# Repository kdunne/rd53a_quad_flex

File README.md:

# RD53A_quad chip hybrid PCB design files

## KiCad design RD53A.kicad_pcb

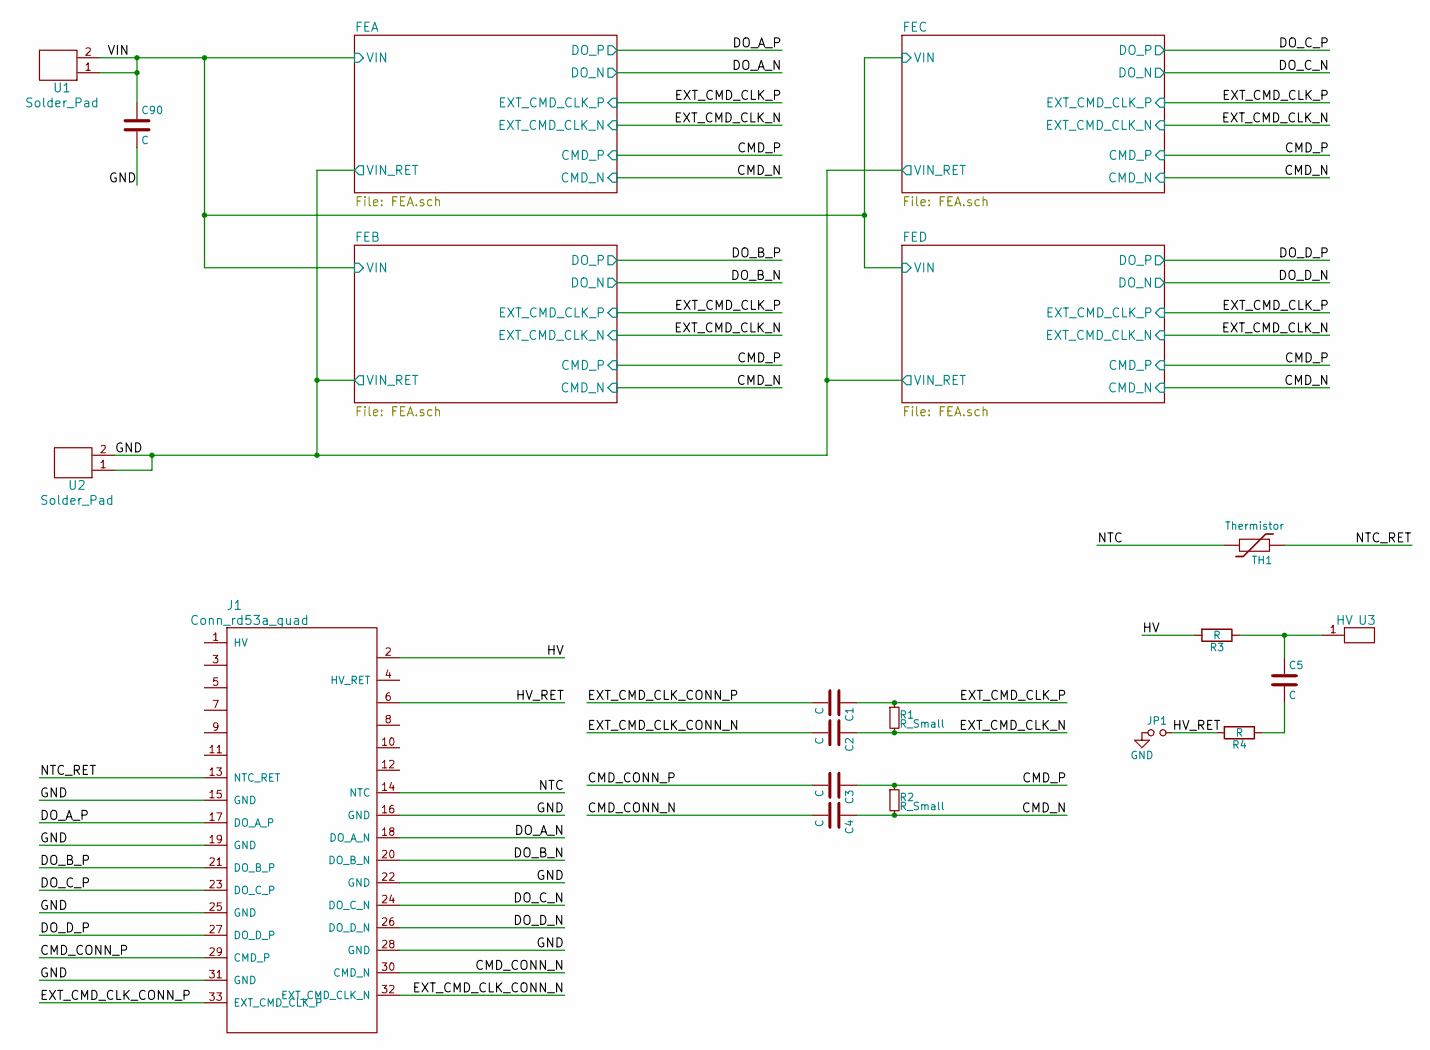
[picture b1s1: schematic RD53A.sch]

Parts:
C1, C2, C3, C4, C90: C; C_0402_NoSilk
C5: C; C_0805
J1: Conn_rd53a_quad; conn
JP1: R_0201_NoSilk
R1, R2: R_Small; R_0402_NoSilk
R3, R4: R; R_0402_NoSilk
TH1: Thermistor; R_0603
U1, U2: Solder_Pad; Power_Pad
U3: HV

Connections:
/CMD_CONN_N: C4.2, J1.30 (CMD_N)
/CMD_CONN_P: C3.2, J1.29 (CMD_P)
/CMD_N: C4.1, R2.2; also elsewhere on the board
/CMD_P: C3.1, R2.1; also elsewhere on the board
/DO_A_N: J1.18 (DO_A_N); also elsewhere on the board
/DO_A_P: J1.17 (DO_A_P); also elsewhere on the board
/DO_B_N: J1.20 (DO_B_N); also elsewhere on the board
/DO_B_P: J1.21 (DO_B_P); also elsewhere on the board
/DO_C_N: J1.24 (DO_C_N); also elsewhere on the board
/DO_C_P: J1.23 (DO_C_P); also elsewhere on the board
/DO_D_N: J1.26 (DO_D_N); also elsewhere on the board
/DO_D_P: J1.27 (DO_D_P); also elsewhere on the board
/EXT_CMD_CLK_CONN_N: C2.2, J1.32 (EXT_CMD_CLK_N)
/EXT_CMD_CLK_CONN_P: C1.2, J1.33 (EXT_CMD_CLK_P)
/EXT_CMD_CLK_N: C2.1, R1.2; also elsewhere on the board
/EXT_CMD_CLK_P: C1.1, R1.1; also elsewhere on the board
/HV: J1.2, R3.2
/HV_RET: J1.6, JP1.2, R4.2
/NTC: J1.14 (NTC), TH1.2
/NTC_RET: J1.13 (NTC_RET), TH1.1
/VIN: C90.1, U1.1, U1.2; also elsewhere on the board
GND: C90.2, J1.15 (GND), J1.16 (GND), J1.19 (GND), J1.22 (GND), J1.25 (GND), J1.28 (GND), J1.31 (GND), JP1.1, U2.1, U2.2; also elsewhere on the board
unnamed: C5.1, R3.1, U3.1
unnamed: C5.2, R4.1

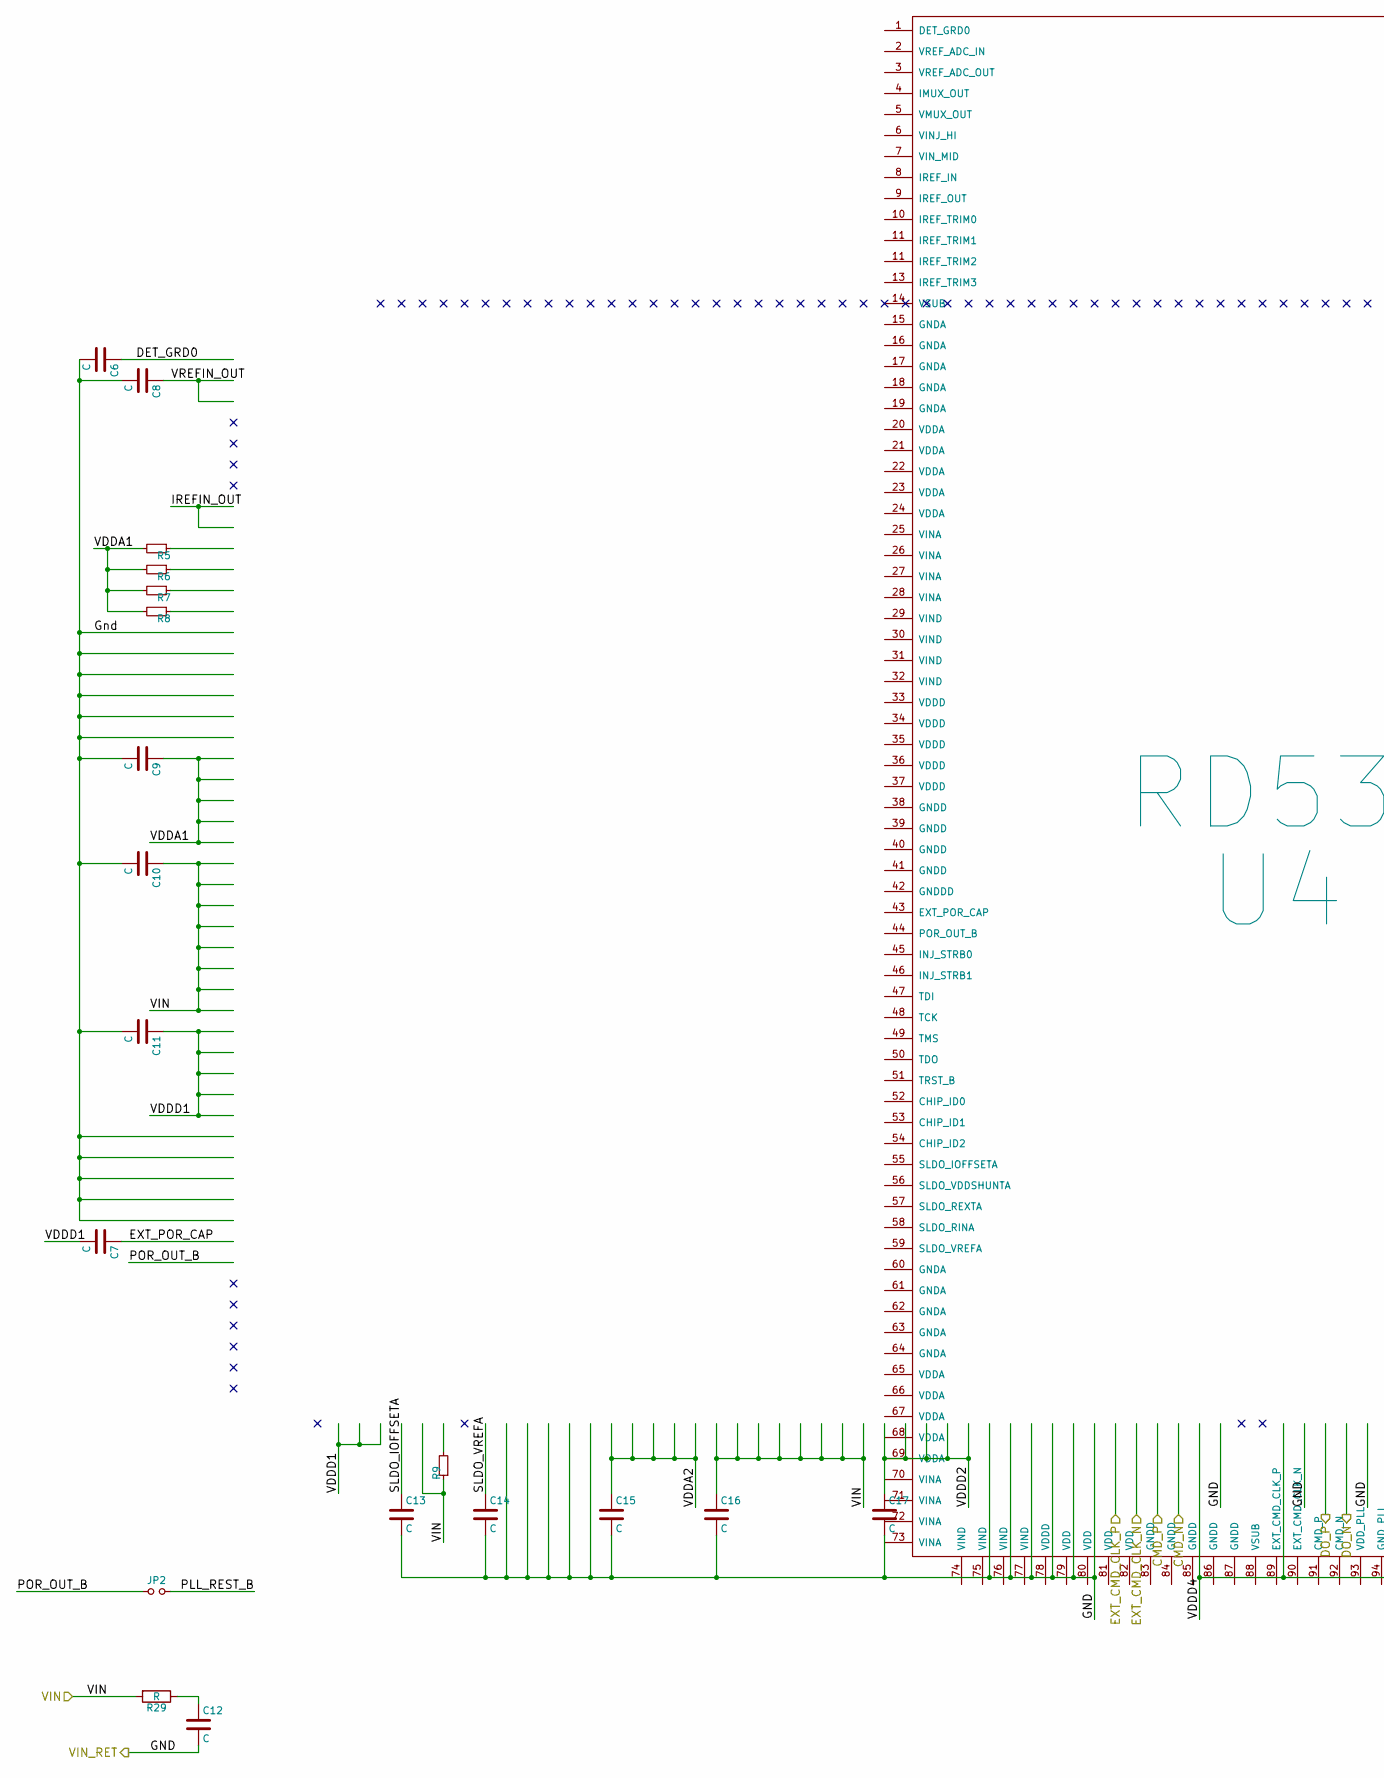
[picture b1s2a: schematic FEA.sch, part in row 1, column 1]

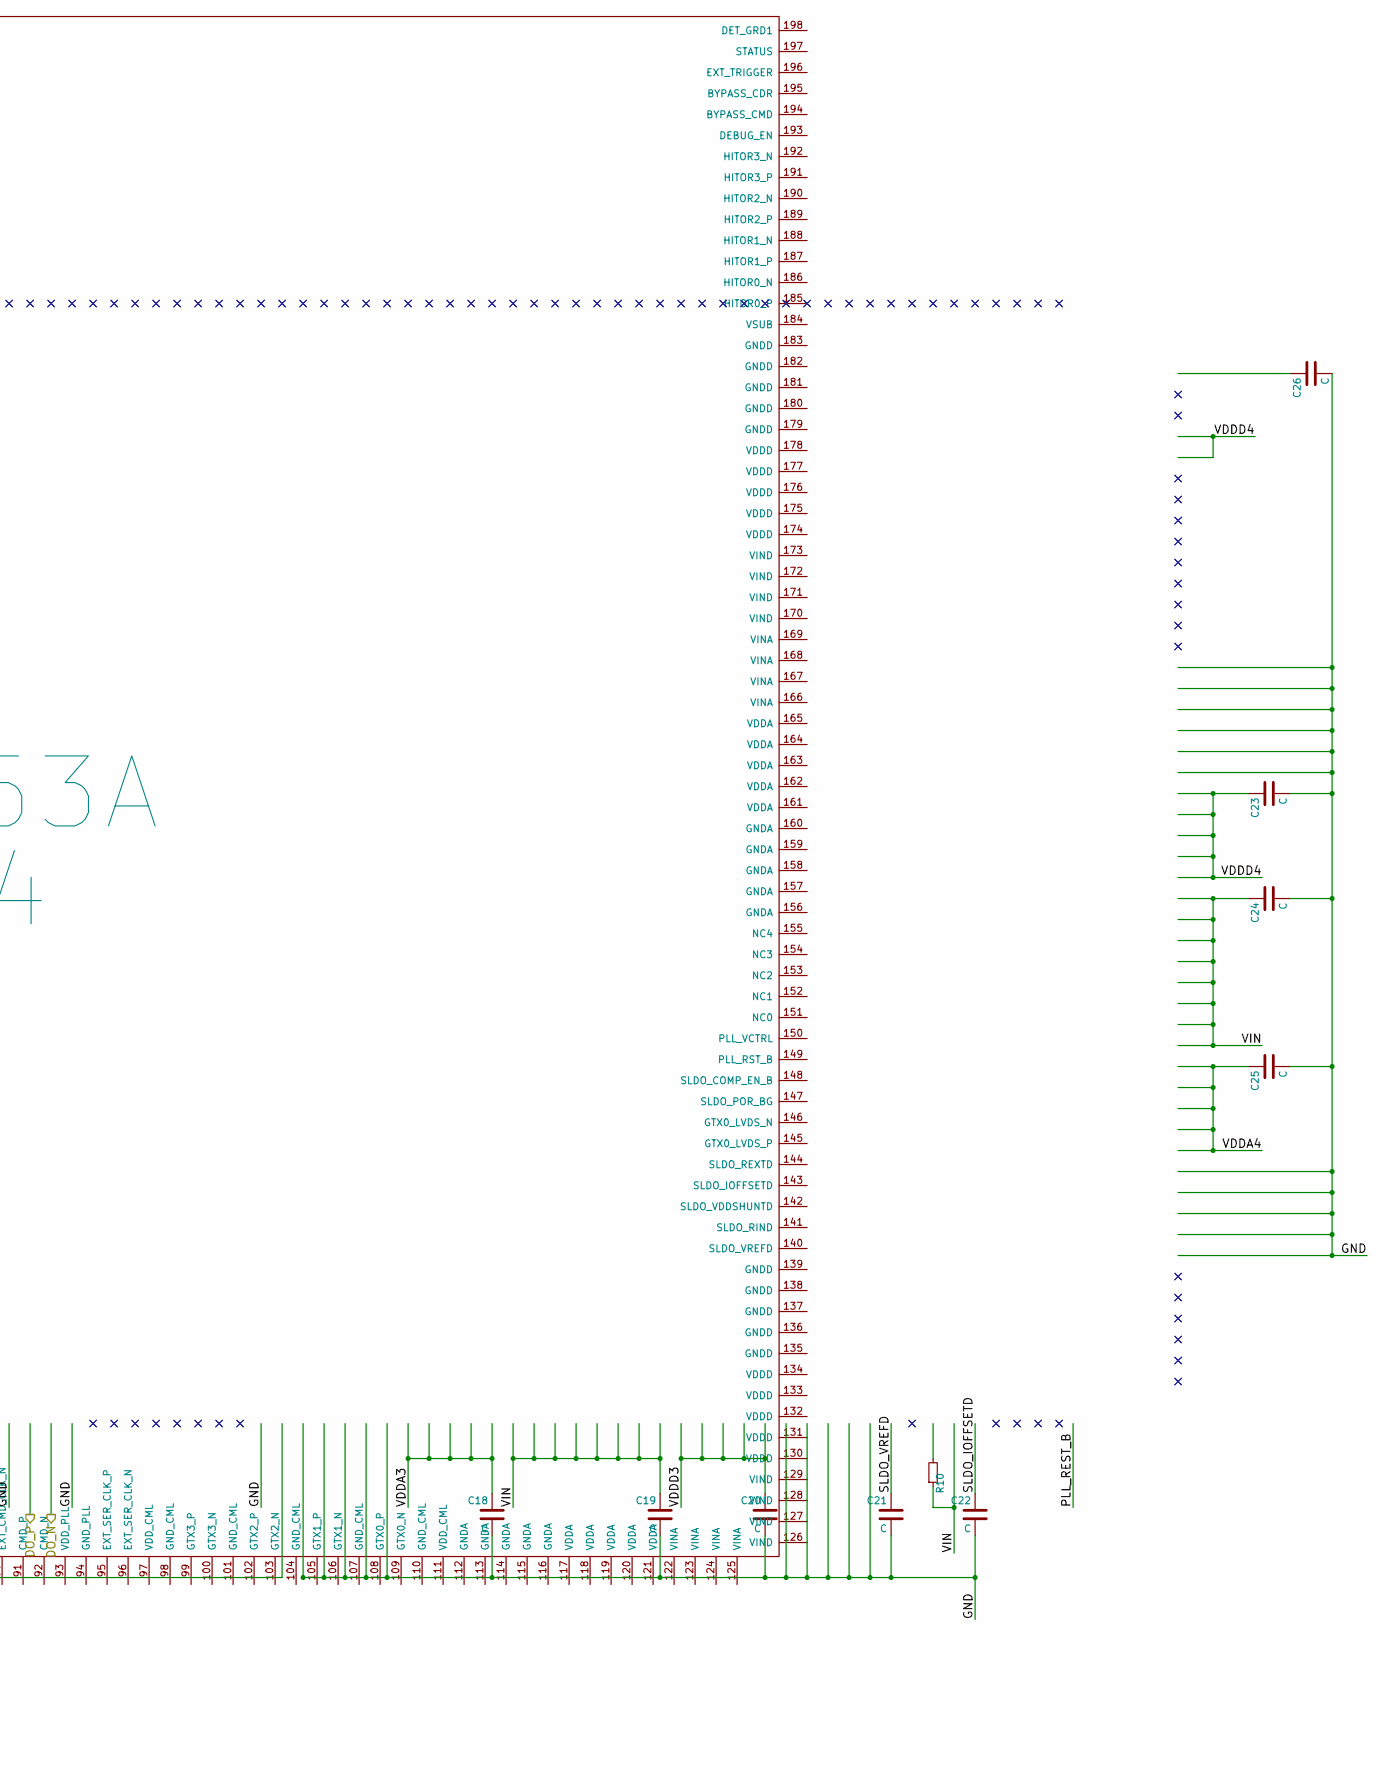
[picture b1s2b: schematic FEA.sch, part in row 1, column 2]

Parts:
C6, C26: C; C_0201_NoSilk
C7, C8, C9, C10, C11, C12, C13, C14, C15, C16, C17, C18, C19, C20, C21, C22, C23, C24, C25: C; C_0402_NoSilk
JP2: C_0201_NoSilk
R5, R6, R7, R8: R_Small; R_0201_NoSilk
R9, R10: R_Small; R_0402_NoSilk
R29: R; R_0402_NoSilk
U4: RD53A; rd53a_wirebonds

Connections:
/CMD_N: U4.92 (CMD_N); also elsewhere on the board
/CMD_P: U4.91 (CMD_P); also elsewhere on the board
/DO_A_N: U4.100 (GTX3_N); also elsewhere on the board
/DO_A_P: U4.99 (GTX3_P); also elsewhere on the board
/EXT_CMD_CLK_N: U4.90 (EXT_CMD_CLK_N); also elsewhere on the board
/EXT_CMD_CLK_P: U4.89 (EXT_CMD_CLK_P); also elsewhere on the board
/FEA/DET_GRD0: C6.1, U4.1 (DET_GRD0)
/FEA/EXT_POR_CAP: C7.1, U4.43 (EXT_POR_CAP)
/FEA/IREFIN_OUT: U4.8 (IREF_IN), U4.9 (IREF_OUT)
/FEA/PLL_REST_B: JP2.2, U4.149 (PLL_RST_B)
/FEA/POR_OUT_B: JP2.1, U4.44 (POR_OUT_B)
/FEA/SLDO_IOFFSETA: C13.1, U4.55 (SLDO_IOFFSETA)
/FEA/SLDO_IOFFSETD: C22.1, U4.144 (SLDO_REXTD)
/FEA/SLDO_VREFA: C14.1, U4.59 (SLDO_VREFA)
/FEA/SLDO_VREFD: C21.1, U4.140 (SLDO_VREFD)
/FEA/VDDA1: C9.1, R5.2, R6.2, R7.2, R8.2, U4.20 (VDDA), U4.21 (VDDA), U4.22 (VDDA), U4.23 (VDDA), U4.24 (VDDA)
/FEA/VDDA3: C18.1, U4.117 (VDDA), U4.118 (VDDA), U4.119 (VDDA), U4.120 (VDDA), U4.121 (VDDA)
/FEA/VDDA4: C25.1, U4.161 (VDDA), U4.162 (VDDA), U4.163 (VDDA), U4.164 (VDDA), U4.165 (VDDA)
/FEA/VDDD1: C7.2, C11.1, U4.33 (VDDD), U4.34 (VDDD), U4.35 (VDDD), U4.36 (VDDD), U4.37 (VDDD), U4.52 (CHIP_ID0), U4.53 (CHIP_ID1), U4.54 (CHIP_ID2)
/FEA/VDDD3: C20.1, U4.130 (VDDD), U4.131 (VDDD), U4.132 (VDDD), U4.133 (VDDD), U4.134 (VDDD)
/FEA/VDDD4: C23.1, U4.93 (VDD_PLL), U4.97 (VDD_CML), U4.111 (VDD_CML), U4.174 (VDDD), U4.175 (VDDD), U4.176 (VDDD), U4.177 (VDDD), U4.178 (VDDD), U4.194 (BYPASS_CMD), U4.195 (BYPASS_CDR)
/FEA/VREFIN_OUT: C8.1, U4.2 (VREF_ADC_IN), U4.3 (VREF_ADC_OUT)
/VIN: C10.1, C16.1, C19.1, C24.1, R9.1, R10.1, R29.2, U4.25 (VINA), U4.26 (VINA), U4.27 (VINA), U4.28 (VINA), U4.29 (VIND), U4.30 (VIND), U4.31 (VIND), U4.32 (VIND), U4.56 (SLDO_VDDSHUNTA), U4.70 (VINA), U4.71 (VINA), U4.72 (VINA), U4.73 (VINA), U4.74 (VIND), U4.75 (VIND), U4.76 (VIND), U4.77 (VIND), U4.122 (VINA), U4.123 (VINA), U4.124 (VINA), U4.125 (VINA), U4.126 (VIND), U4.127 (VIND), U4.128 (VIND), U4.129 (VIND), U4.143 (SLDO_IOFFSETD), U4.166 (VINA), U4.167 (VINA), U4.168 (VINA), U4.169 (VINA), U4.170 (VIND), U4.171 (VIND), U4.172 (VIND), U4.173 (VIND); also elsewhere on the board
GND: C6.2, C8.2, C9.2, C10.2, C11.2, C12.2, C13.2, C14.2, C15.2, C16.2, C17.2, C18.2, C19.2, C20.2, C21.2, C22.2, C23.2, C24.2, C25.2, C26.2, U4.14 (VSUB), U4.15 (GNDA), U4.16 (GNDA), U4.17 (GNDA), U4.18 (GNDA), U4.19 (GNDA), U4.38 (GNDD), U4.39 (GNDD), U4.40 (GNDD), U4.41 (GNDD), U4.42 (GNDDD), U4.60 (GNDA), U4.61 (GNDA), U4.62 (GNDA), U4.63 (GNDA), U4.64 (GNDA), U4.83 (GNDD), U4.84 (GNDD), U4.85 (GNDD), U4.86 (GNDD), U4.87 (GNDD), U4.88 (VSUB), U4.94 (GND_PLL), U4.98 (GND_CML), U4.101 (GND_CML), U4.110 (GND_CML), U4.112 (GNDA), U4.113 (GNDA), U4.114 (GNDA), U4.115 (GNDA), U4.116 (GNDA), U4.135 (GNDD), U4.136 (GNDD), U4.137 (GNDD), U4.138 (GNDD), U4.139 (GNDD), U4.156 (GNDA), U4.157 (GNDA), U4.158 (GNDA), U4.159 (GNDA), U4.160 (GNDA), U4.179 (GNDD), U4.180 (GNDD), U4.181 (GNDD), U4.182 (GNDD), U4.183 (GNDD), U4.184 (VSUB); also elsewhere on the board
unnamed: C12.1, R29.1
unnamed: C26.1, U4.198 (DET_GRD1)
unnamed: R5.1, U4.10 (IREF_TRIM0)
unnamed: R6.1, U4.11 (IREF_TRIM1)
unnamed: R7.1, U4.12 (IREF_TRIM2)
unnamed: R8.1, U4.13 (IREF_TRIM3)
unnamed: R9.2, U4.57 (SLDO_REXTA)
unnamed: R10.2, U4.142 (SLDO_VDDSHUNTD)

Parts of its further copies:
C27, C47, C48, C68, C69, C89: C; C_0201_NoSilk
C28, C29, C30, C31, C32, C33, C34, C35, C36, C37, C38, C39, C40, C41, C42, C43, C44, C45, C46, C49, C50, C51, C52, C53, C54, C55, C56, C57, C58, C59, C60, C61, C62, C63, C64, C65, C66, C67, C70, C71, C72, C73, C74, C75, C76, C77, C78, C79, C80, C81, C82, C83, C84, C85, C86, C87, C88: C; C_0402_NoSilk
JP3, JP4, JP5: C_0201_NoSilk
R11, R12, R13, R14, R17, R18, R19, R20, R23, R24, R25, R26: R_Small; R_0201_NoSilk
R15, R16, R21, R22, R27, R28: R_Small; R_0402_NoSilk
R30, R31, R32: R; R_0402_NoSilk
U5, U6, U7: RD53A; rd53a_wirebonds

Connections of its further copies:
/CMD_N: U5.92 (CMD_N), U6.92 (CMD_N), U7.92 (CMD_N); also elsewhere on the board
/CMD_P: U5.91 (CMD_P), U6.91 (CMD_P), U7.91 (CMD_P); also elsewhere on the board
/DO_B_N: U5.100 (GTX3_N); also elsewhere on the board
/DO_B_P: U5.99 (GTX3_P); also elsewhere on the board
/DO_C_N: U6.100 (GTX3_N); also elsewhere on the board
/DO_C_P: U6.99 (GTX3_P); also elsewhere on the board
/DO_D_N: U7.100 (GTX3_N); also elsewhere on the board
/DO_D_P: U7.99 (GTX3_P); also elsewhere on the board
/EXT_CMD_CLK_N: U5.90 (EXT_CMD_CLK_N), U6.90 (EXT_CMD_CLK_N), U7.90 (EXT_CMD_CLK_N); also elsewhere on the board
/EXT_CMD_CLK_P: U5.89 (EXT_CMD_CLK_P), U6.89 (EXT_CMD_CLK_P), U7.89 (EXT_CMD_CLK_P); also elsewhere on the board
/FEB/DET_GRD0: C27.1, U5.1 (DET_GRD0)
/FEB/EXT_POR_CAP: C28.1, U5.43 (EXT_POR_CAP)
/FEB/IREFIN_OUT: U5.8 (IREF_IN), U5.9 (IREF_OUT)
/FEB/PLL_REST_B: JP3.2, U5.149 (PLL_RST_B)
/FEB/POR_OUT_B: JP3.1, U5.44 (POR_OUT_B)
/FEB/SLDO_IOFFSETA: C34.1, U5.55 (SLDO_IOFFSETA)
/FEB/SLDO_IOFFSETD: C43.1, U5.144 (SLDO_REXTD)
/FEB/SLDO_VREFA: C35.1, U5.59 (SLDO_VREFA)
/FEB/SLDO_VREFD: C42.1, U5.140 (SLDO_VREFD)
/FEB/VDDA1: C30.1, R11.2, R12.2, R13.2, R14.2, U5.20 (VDDA), U5.21 (VDDA), U5.22 (VDDA), U5.23 (VDDA), U5.24 (VDDA)
/FEB/VDDA2: C36.1, U5.65 (VDDA), U5.66 (VDDA), U5.67 (VDDA), U5.68 (VDDA), U5.69 (VDDA)
/FEB/VDDA3: C39.1, U5.117 (VDDA), U5.118 (VDDA), U5.119 (VDDA), U5.120 (VDDA), U5.121 (VDDA)
/FEB/VDDA4: C46.1, U5.161 (VDDA), U5.162 (VDDA), U5.163 (VDDA), U5.164 (VDDA), U5.165 (VDDA)
/FEB/VDDD1: C28.2, C32.1, U5.33 (VDDD), U5.34 (VDDD), U5.35 (VDDD), U5.36 (VDDD), U5.37 (VDDD), U5.52 (CHIP_ID0), U5.53 (CHIP_ID1), U5.54 (CHIP_ID2)
/FEB/VDDD2: C38.1, U5.78 (VDDD), U5.79 (VDD), U5.80 (VDD), U5.81 (VDD), U5.82 (VDD)
/FEB/VDDD3: C41.1, U5.130 (VDDD), U5.131 (VDDD), U5.132 (VDDD), U5.133 (VDDD), U5.134 (VDDD)
/FEB/VDDD4: C44.1, U5.93 (VDD_PLL), U5.97 (VDD_CML), U5.111 (VDD_CML), U5.174 (VDDD), U5.175 (VDDD), U5.176 (VDDD), U5.177 (VDDD), U5.178 (VDDD), U5.194 (BYPASS_CMD), U5.195 (BYPASS_CDR)
/FEB/VREFIN_OUT: C29.1, U5.2 (VREF_ADC_IN), U5.3 (VREF_ADC_OUT)
/FEC/DET_GRD0: C48.1, U6.1 (DET_GRD0)
/FEC/EXT_POR_CAP: C49.1, U6.43 (EXT_POR_CAP)
/FEC/IREFIN_OUT: U6.8 (IREF_IN), U6.9 (IREF_OUT)
/FEC/PLL_REST_B: JP4.2, U6.149 (PLL_RST_B)
/FEC/POR_OUT_B: JP4.1, U6.44 (POR_OUT_B)
/FEC/SLDO_IOFFSETA: C55.1, U6.55 (SLDO_IOFFSETA)
/FEC/SLDO_IOFFSETD: C64.1, U6.144 (SLDO_REXTD)
/FEC/SLDO_VREFA: C56.1, U6.59 (SLDO_VREFA)
/FEC/SLDO_VREFD: C63.1, U6.140 (SLDO_VREFD)
/FEC/VDDA1: C51.1, R17.2, R18.2, R19.2, R20.2, U6.20 (VDDA), U6.21 (VDDA), U6.22 (VDDA), U6.23 (VDDA), U6.24 (VDDA)
/FEC/VDDA2: C57.1, U6.65 (VDDA), U6.66 (VDDA), U6.67 (VDDA), U6.68 (VDDA), U6.69 (VDDA)
/FEC/VDDA3: C60.1, U6.117 (VDDA), U6.118 (VDDA), U6.119 (VDDA), U6.120 (VDDA), U6.121 (VDDA)
/FEC/VDDA4: C67.1, U6.161 (VDDA), U6.162 (VDDA), U6.163 (VDDA), U6.164 (VDDA), U6.165 (VDDA)
/FEC/VDDD1: C49.2, C53.1, U6.33 (VDDD), U6.34 (VDDD), U6.35 (VDDD), U6.36 (VDDD), U6.37 (VDDD), U6.52 (CHIP_ID0), U6.53 (CHIP_ID1), U6.54 (CHIP_ID2)
/FEC/VDDD2: C59.1, U6.78 (VDDD), U6.79 (VDD), U6.80 (VDD), U6.81 (VDD), U6.82 (VDD)
/FEC/VDDD3: C62.1, U6.130 (VDDD), U6.131 (VDDD), U6.132 (VDDD), U6.133 (VDDD), U6.134 (VDDD)
/FEC/VDDD4: C65.1, U6.93 (VDD_PLL), U6.97 (VDD_CML), U6.111 (VDD_CML), U6.174 (VDDD), U6.175 (VDDD), U6.176 (VDDD), U6.177 (VDDD), U6.178 (VDDD), U6.194 (BYPASS_CMD), U6.195 (BYPASS_CDR)
/FEC/VREFIN_OUT: C50.1, U6.2 (VREF_ADC_IN), U6.3 (VREF_ADC_OUT)
/FED/DET_GRD0: C69.1, U7.1 (DET_GRD0)
/FED/EXT_POR_CAP: C70.1, U7.43 (EXT_POR_CAP)
/FED/IREFIN_OUT: U7.8 (IREF_IN), U7.9 (IREF_OUT)
/FED/PLL_REST_B: JP5.2, U7.149 (PLL_RST_B)
/FED/POR_OUT_B: JP5.1, U7.44 (POR_OUT_B)
/FED/SLDO_IOFFSETA: C76.1, U7.55 (SLDO_IOFFSETA)
/FED/SLDO_IOFFSETD: C85.1, U7.144 (SLDO_REXTD)
/FED/SLDO_VREFA: C77.1, U7.59 (SLDO_VREFA)
/FED/SLDO_VREFD: C84.1, U7.140 (SLDO_VREFD)
/FED/VDDA1: C72.1, R23.2, R24.2, R25.2, R26.2, U7.20 (VDDA), U7.21 (VDDA), U7.22 (VDDA), U7.23 (VDDA), U7.24 (VDDA)
/FED/VDDA2: C78.1, U7.65 (VDDA), U7.66 (VDDA), U7.67 (VDDA), U7.68 (VDDA), U7.69 (VDDA)
/FED/VDDA3: C81.1, U7.117 (VDDA), U7.118 (VDDA), U7.119 (VDDA), U7.120 (VDDA), U7.121 (VDDA)
/FED/VDDA4: C88.1, U7.161 (VDDA), U7.162 (VDDA), U7.163 (VDDA), U7.164 (VDDA), U7.165 (VDDA)
/FED/VDDD1: C70.2, C74.1, U7.33 (VDDD), U7.34 (VDDD), U7.35 (VDDD), U7.36 (VDDD), U7.37 (VDDD), U7.52 (CHIP_ID0), U7.53 (CHIP_ID1), U7.54 (CHIP_ID2)
/FED/VDDD2: C80.1, U7.78 (VDDD), U7.79 (VDD), U7.80 (VDD), U7.81 (VDD), U7.82 (VDD)
/FED/VDDD3: C83.1, U7.130 (VDDD), U7.131 (VDDD), U7.132 (VDDD), U7.133 (VDDD), U7.134 (VDDD)
/FED/VDDD4: C86.1, U7.93 (VDD_PLL), U7.97 (VDD_CML), U7.111 (VDD_CML), U7.174 (VDDD), U7.175 (VDDD), U7.176 (VDDD), U7.177 (VDDD), U7.178 (VDDD), U7.194 (BYPASS_CMD), U7.195 (BYPASS_CDR)
/FED/VREFIN_OUT: C71.1, U7.2 (VREF_ADC_IN), U7.3 (VREF_ADC_OUT)
/VIN: C31.1, C37.1, C40.1, C45.1, C52.1, C58.1, C61.1, C66.1, C73.1, C79.1, C82.1, C87.1, R15.1, R16.1, R21.1, R22.1, R27.1, R28.1, R30.2, R31.2, R32.2, U5.25 (VINA), U5.26 (VINA), U5.27 (VINA), U5.28 (VINA), U5.29 (VIND), U5.30 (VIND), U5.31 (VIND), U5.32 (VIND), U5.56 (SLDO_VDDSHUNTA), U5.70 (VINA), U5.71 (VINA), U5.72 (VINA), U5.73 (VINA), U5.74 (VIND), U5.75 (VIND), U5.76 (VIND), U5.77 (VIND), U5.122 (VINA), U5.123 (VINA), U5.124 (VINA), U5.125 (VINA), U5.126 (VIND), U5.127 (VIND), U5.128 (VIND), U5.129 (VIND), U5.143 (SLDO_IOFFSETD), U5.166 (VINA), U5.167 (VINA), U5.168 (VINA), U5.169 (VINA), U5.170 (VIND), U5.171 (VIND), U5.172 (VIND), U5.173 (VIND), U6.25 (VINA), U6.26 (VINA), U6.27 (VINA), U6.28 (VINA), U6.29 (VIND), U6.30 (VIND), U6.31 (VIND), U6.32 (VIND), U6.56 (SLDO_VDDSHUNTA), U6.70 (VINA), U6.71 (VINA), U6.72 (VINA), U6.73 (VINA), U6.74 (VIND), U6.75 (VIND), U6.76 (VIND), U6.77 (VIND), U6.122 (VINA), U6.123 (VINA), U6.124 (VINA), U6.125 (VINA), U6.126 (VIND), U6.127 (VIND), U6.128 (VIND), U6.129 (VIND), U6.143 (SLDO_IOFFSETD), U6.166 (VINA), U6.167 (VINA), U6.168 (VINA), U6.169 (VINA), U6.170 (VIND), U6.171 (VIND), U6.172 (VIND), U6.173 (VIND), U7.25 (VINA), U7.26 (VINA), U7.27 (VINA), U7.28 (VINA), U7.29 (VIND), U7.30 (VIND), U7.31 (VIND), U7.32 (VIND), U7.56 (SLDO_VDDSHUNTA), U7.70 (VINA), U7.71 (VINA), U7.72 (VINA), U7.73 (VINA), U7.74 (VIND), U7.75 (VIND), U7.76 (VIND), U7.77 (VIND), U7.122 (VINA), U7.123 (VINA), U7.124 (VINA), U7.125 (VINA), U7.126 (VIND), U7.127 (VIND), U7.128 (VIND), U7.129 (VIND), U7.143 (SLDO_IOFFSETD), U7.166 (VINA), U7.167 (VINA), U7.168 (VINA), U7.169 (VINA), U7.170 (VIND), U7.171 (VIND), U7.172 (VIND), U7.173 (VIND); also elsewhere on the board
GND: C27.2, C29.2, C30.2, C31.2, C32.2, C33.2, C34.2, C35.2, C36.2, C37.2, C38.2, C39.2, C40.2, C41.2, C42.2, C43.2, C44.2, C45.2, C46.2, C47.2, C48.2, C50.2, C51.2, C52.2, C53.2, C54.2, C55.2, C56.2, C57.2, C58.2, C59.2, C60.2, C61.2, C62.2, C63.2, C64.2, C65.2, C66.2, C67.2, C68.2, C69.2, C71.2, C72.2, C73.2, C74.2, C75.2, C76.2, C77.2, C78.2, C79.2, C80.2, C81.2, C82.2, C83.2, C84.2, C85.2, C86.2, C87.2, C88.2, C89.2, U5.14 (VSUB), U5.15 (GNDA), U5.16 (GNDA), U5.17 (GNDA), U5.18 (GNDA), U5.19 (GNDA), U5.38 (GNDD), U5.39 (GNDD), U5.40 (GNDD), U5.41 (GNDD), U5.42 (GNDDD), U5.60 (GNDA), U5.61 (GNDA), U5.62 (GNDA), U5.63 (GNDA), U5.64 (GNDA), U5.83 (GNDD), U5.84 (GNDD), U5.85 (GNDD), U5.86 (GNDD), U5.87 (GNDD), U5.88 (VSUB), U5.94 (GND_PLL), U5.98 (GND_CML), U5.101 (GND_CML), U5.110 (GND_CML), U5.112 (GNDA), U5.113 (GNDA), U5.114 (GNDA), U5.115 (GNDA), U5.116 (GNDA), U5.135 (GNDD), U5.136 (GNDD), U5.137 (GNDD), U5.138 (GNDD), U5.139 (GNDD), U5.156 (GNDA), U5.157 (GNDA), U5.158 (GNDA), U5.159 (GNDA), U5.160 (GNDA), U5.179 (GNDD), U5.180 (GNDD), U5.181 (GNDD), U5.182 (GNDD), U5.183 (GNDD), U5.184 (VSUB), U6.14 (VSUB), U6.15 (GNDA), U6.16 (GNDA), U6.17 (GNDA), U6.18 (GNDA), U6.19 (GNDA), U6.38 (GNDD), U6.39 (GNDD), U6.40 (GNDD), U6.41 (GNDD), U6.42 (GNDDD), U6.60 (GNDA), U6.61 (GNDA), U6.62 (GNDA), U6.63 (GNDA), U6.64 (GNDA), U6.83 (GNDD), U6.84 (GNDD), U6.85 (GNDD), U6.86 (GNDD), U6.87 (GNDD), U6.88 (VSUB), U6.94 (GND_PLL), U6.98 (GND_CML), U6.101 (GND_CML), U6.110 (GND_CML), U6.112 (GNDA), U6.113 (GNDA), U6.114 (GNDA), U6.115 (GNDA), U6.116 (GNDA), U6.135 (GNDD), U6.136 (GNDD), U6.137 (GNDD), U6.138 (GNDD), U6.139 (GNDD), U6.156 (GNDA), U6.157 (GNDA), U6.158 (GNDA), U6.159 (GNDA), U6.160 (GNDA), U6.179 (GNDD), U6.180 (GNDD), U6.181 (GNDD), U6.182 (GNDD), U6.183 (GNDD), U6.184 (VSUB), U7.14 (VSUB), U7.15 (GNDA), U7.16 (GNDA), U7.17 (GNDA), U7.18 (GNDA), U7.19 (GNDA), U7.38 (GNDD), U7.39 (GNDD), U7.40 (GNDD), U7.41 (GNDD), U7.42 (GNDDD), U7.60 (GNDA), U7.61 (GNDA), U7.62 (GNDA), U7.63 (GNDA), U7.64 (GNDA), U7.83 (GNDD), U7.84 (GNDD), U7.85 (GNDD), U7.86 (GNDD), U7.87 (GNDD), U7.88 (VSUB), U7.94 (GND_PLL), U7.98 (GND_CML), U7.101 (GND_CML), U7.110 (GND_CML), U7.112 (GNDA), U7.113 (GNDA), U7.114 (GNDA), U7.115 (GNDA), U7.116 (GNDA), U7.135 (GNDD), U7.136 (GNDD), U7.137 (GNDD), U7.138 (GNDD), U7.139 (GNDD), U7.156 (GNDA), U7.157 (GNDA), U7.158 (GNDA), U7.159 (GNDA), U7.160 (GNDA), U7.179 (GNDD), U7.180 (GNDD), U7.181 (GNDD), U7.182 (GNDD), U7.183 (GNDD), U7.184 (VSUB); also elsewhere on the board
unnamed: C33.1, R30.1
unnamed: C47.1, U5.198 (DET_GRD1)
unnamed: C54.1, R31.1
unnamed: C68.1, U6.198 (DET_GRD1)
unnamed: C75.1, R32.1
unnamed: C89.1, U7.198 (DET_GRD1)
unnamed: R11.1, U5.10 (IREF_TRIM0)
unnamed: R12.1, U5.11 (IREF_TRIM1)
unnamed: R13.1, U5.12 (IREF_TRIM2)
unnamed: R14.1, U5.13 (IREF_TRIM3)
unnamed: R15.2, U5.57 (SLDO_REXTA)
unnamed: R16.2, U5.142 (SLDO_VDDSHUNTD)
unnamed: R17.1, U6.10 (IREF_TRIM0)
unnamed: R18.1, U6.11 (IREF_TRIM1)
unnamed: R19.1, U6.12 (IREF_TRIM2)
unnamed: R20.1, U6.13 (IREF_TRIM3)
unnamed: R21.2, U6.57 (SLDO_REXTA)
unnamed: R22.2, U6.142 (SLDO_VDDSHUNTD)
unnamed: R23.1, U7.10 (IREF_TRIM0)
unnamed: R24.1, U7.11 (IREF_TRIM1)
unnamed: R25.1, U7.12 (IREF_TRIM2)
unnamed: R26.1, U7.13 (IREF_TRIM3)
unnamed: R27.2, U7.57 (SLDO_REXTA)
unnamed: R28.2, U7.142 (SLDO_VDDSHUNTD)

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
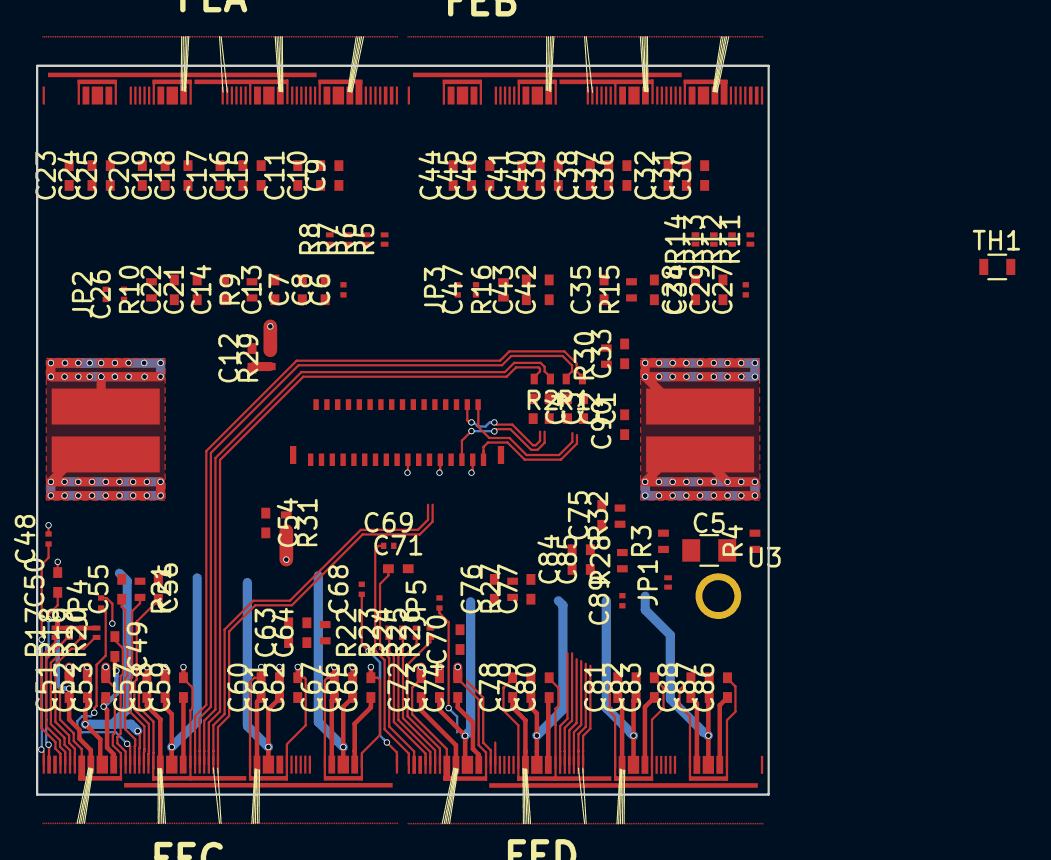
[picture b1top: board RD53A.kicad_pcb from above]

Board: 2 copper layers, 40.6 x 40.5 mm, 136 parts (0 on the bottom side), 128 nets.

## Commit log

2017-07-13 Create RD53A component
2017-07-13 Create Front end hierarchical sheets
2017-07-13 Add top row pins to RD53A
2017-07-13 Clean up RD53A pins
2017-07-25 Replace multiple caps with one
2017-08-24 Create schematic, board dimensions in PCBnew
2017-08-25 remove backup files
2017-08-26 Add connector board, replace DETGRND jumpers with capacitors
2017-08-29 Place all components on board, begin power distribution layout
2017-09-05 Route power and components for bottom left front end
2017-09-21 Update Digital SLDO pins
